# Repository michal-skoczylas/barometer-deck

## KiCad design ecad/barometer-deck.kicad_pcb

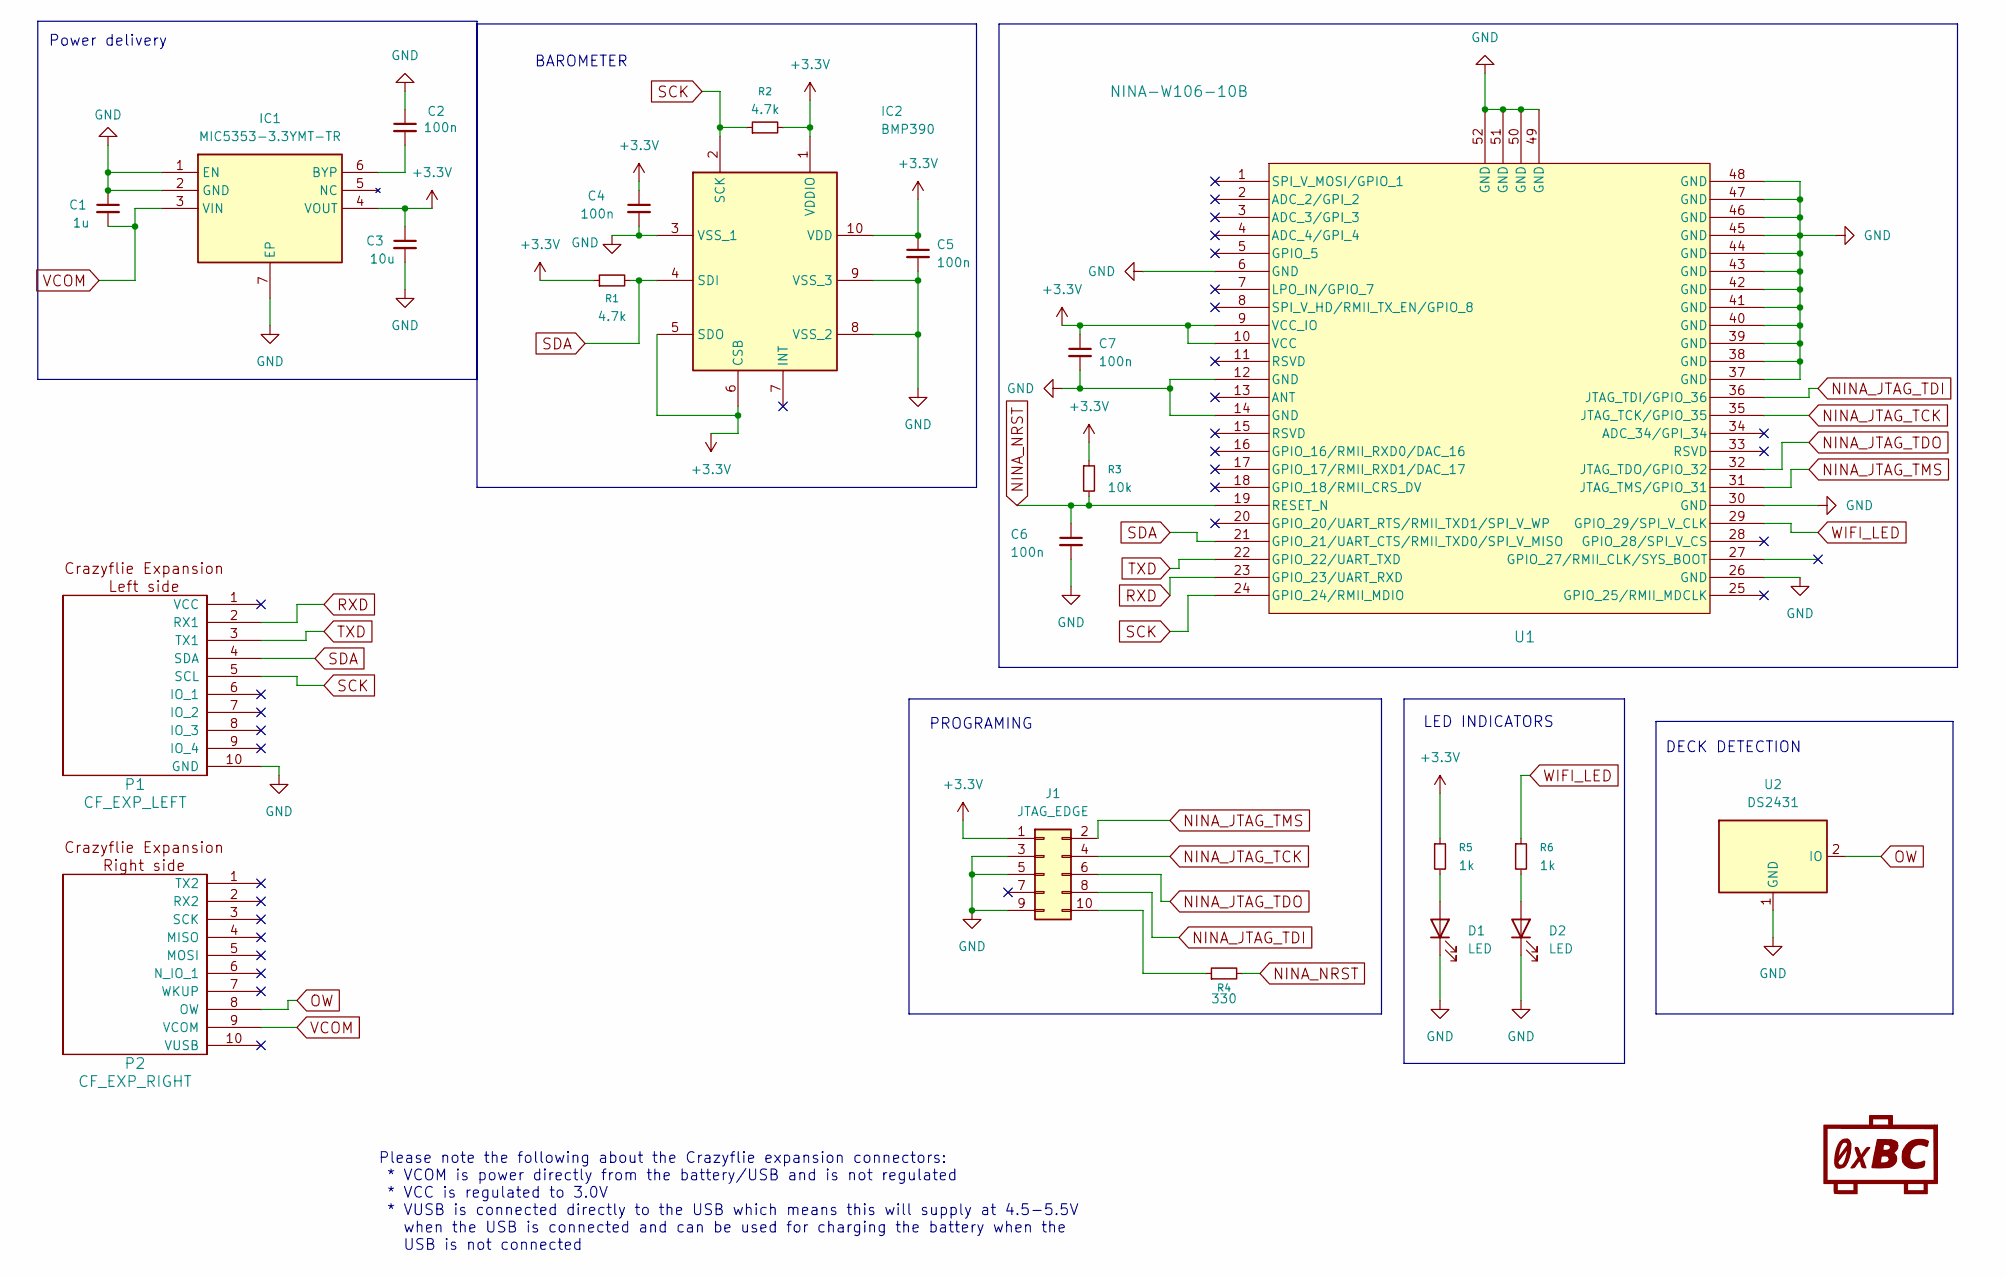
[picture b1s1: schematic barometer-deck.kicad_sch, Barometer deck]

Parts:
B1: bitcraze_200
C1: 1u; C_0402_1005Metric
C2, C4, C5, C6, C7: 100n; C_0402_1005Metric
C3: 10u; C_0402_1005Metric
D1, D2: LED; LED_0603_1608Metric
IC1: MIC5353-3.3YMT-TR; SON50P160X160X60-7N-D; Mouser Part Number 998-MIC5353-3.3YMTTR
IC2: BMP390; Mouser Part Number 262-BMP390
J1: JTAG_EDGE; PinHeader_2x05_P1.27mm_Horizontal
P1: CF_EXP_LEFT; PinSocket_1x10_P2.00mm_Vertical
P2: CF_EXP_RIGHT; PinSocket_1x10_P2.00mm_Vertical
R1, R2: 4.7k; R_0402_1005Metric
R3: 10k; R_0402_1005Metric
R4: 330; R_0402_1005Metric
R5, R6: 1k; R_0402_1005Metric
U1: NINA-W106-10B; NINA-W106_UBL
U2: DS2431; SOT-23-3

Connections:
+3.3V: C3.1, C4.1, C5.1, C7.1, IC1.4 (VOUT), IC2.1 (VDDIO), IC2.5 (SDO), IC2.6 (CSB), IC2.10 (VDD), J1.1, R1.1, R2.2, R3.1, R5.1, U1.9 (VCC_IO), U1.10 (VCC)
GND: C1.1, C2.1, C3.2, C4.2, C5.2, C6.2, C7.2, D1.1 (K), D2.1 (K), IC1.1 (EN), IC1.2 (GND), IC1.7 (EP), IC2.3 (VSS_1), IC2.8 (VSS_2), IC2.9 (VSS_3), J1.3, J1.5, J1.9, P1.10 (GND), U1.6 (GND), U1.12 (GND), U1.14 (GND), U1.26 (GND), U1.30 (GND), U1.37 (GND), U1.38 (GND), U1.39 (GND), U1.40 (GND), U1.41 (GND), U1.42 (GND), U1.43 (GND), U1.44 (GND), U1.45 (GND), U1.46 (GND), U1.47 (GND), U1.48 (GND), U1.49 (GND), U1.50 (GND), U1.51 (GND), U1.52 (GND), U2.1 (GND)
NINA_JTAG_TCK: J1.4, U1.35 (JTAG_TCK/GPIO_35)
NINA_JTAG_TDI: J1.8, U1.36 (JTAG_TDI/GPIO_36)
NINA_JTAG_TDO: J1.6, U1.32 (JTAG_TDO/GPIO_32)
NINA_JTAG_TMS: J1.2, U1.31 (JTAG_TMS/GPIO_31)
NINA_NRST: C6.1, R3.2, R4.2, U1.19 (RESET_N)
unnamed: D1.2 (A), R5.2
unnamed: D2.2 (A), R6.2
unnamed: C2.2, IC1.6 (BYP)
unnamed: J1.10, R4.1
OW: P2.8 (OW), U2.2 (IO)
RXD: P1.2 (RX1), U1.23 (GPIO_23/UART_RXD)
SCK: IC2.2 (SCK), P1.5 (SCL), R2.1, U1.24 (GPIO_24/RMII_MDIO)
SDA: IC2.4 (SDI), P1.4 (SDA), R1.2, U1.21 (GPIO_21/UART_CTS/RMII_TXD0/SPI_V_MISO)
TXD: P1.3 (TX1), U1.22 (GPIO_22/UART_TXD)
VCOM: C1.2, IC1.3 (VIN), P2.9 (VCOM)
WIFI_LED: R6.1, U1.29 (GPIO_29/SPI_V_CLK)

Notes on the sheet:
PROGRAMING
DECK DETECTION
LED INDICATORS
Please note the following about the Crazyflie expansion connectors: * VCOM is power directly from the battery/USB and is not regulated * VCC is regulated to 3.0V * VUSB is connected directly to the USB which means this will supply at 4.5-5.5V when the USB is connected and can be used for charging t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
Power delivery
BAROMETER

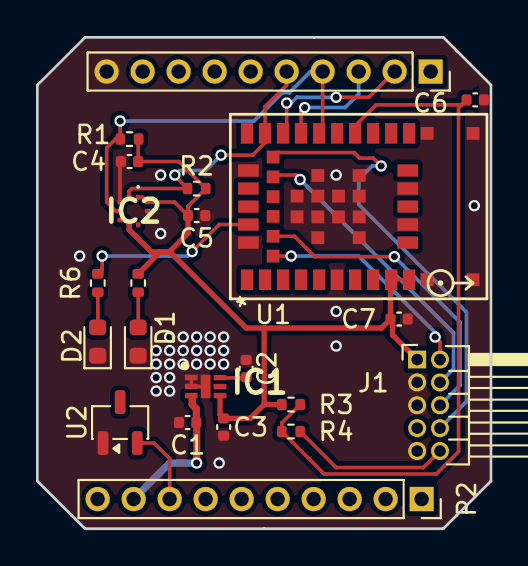
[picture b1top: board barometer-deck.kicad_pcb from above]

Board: 2 copper layers, 25.2 x 27.3 mm, 23 parts (0 on the bottom side), 18 nets.

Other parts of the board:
EXP_ORIENTATION: VAL**; EXP_ORIENTATION

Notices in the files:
ecad/barometer-deck.kicad_pcb:
Licensed under CC-BY 4.0
